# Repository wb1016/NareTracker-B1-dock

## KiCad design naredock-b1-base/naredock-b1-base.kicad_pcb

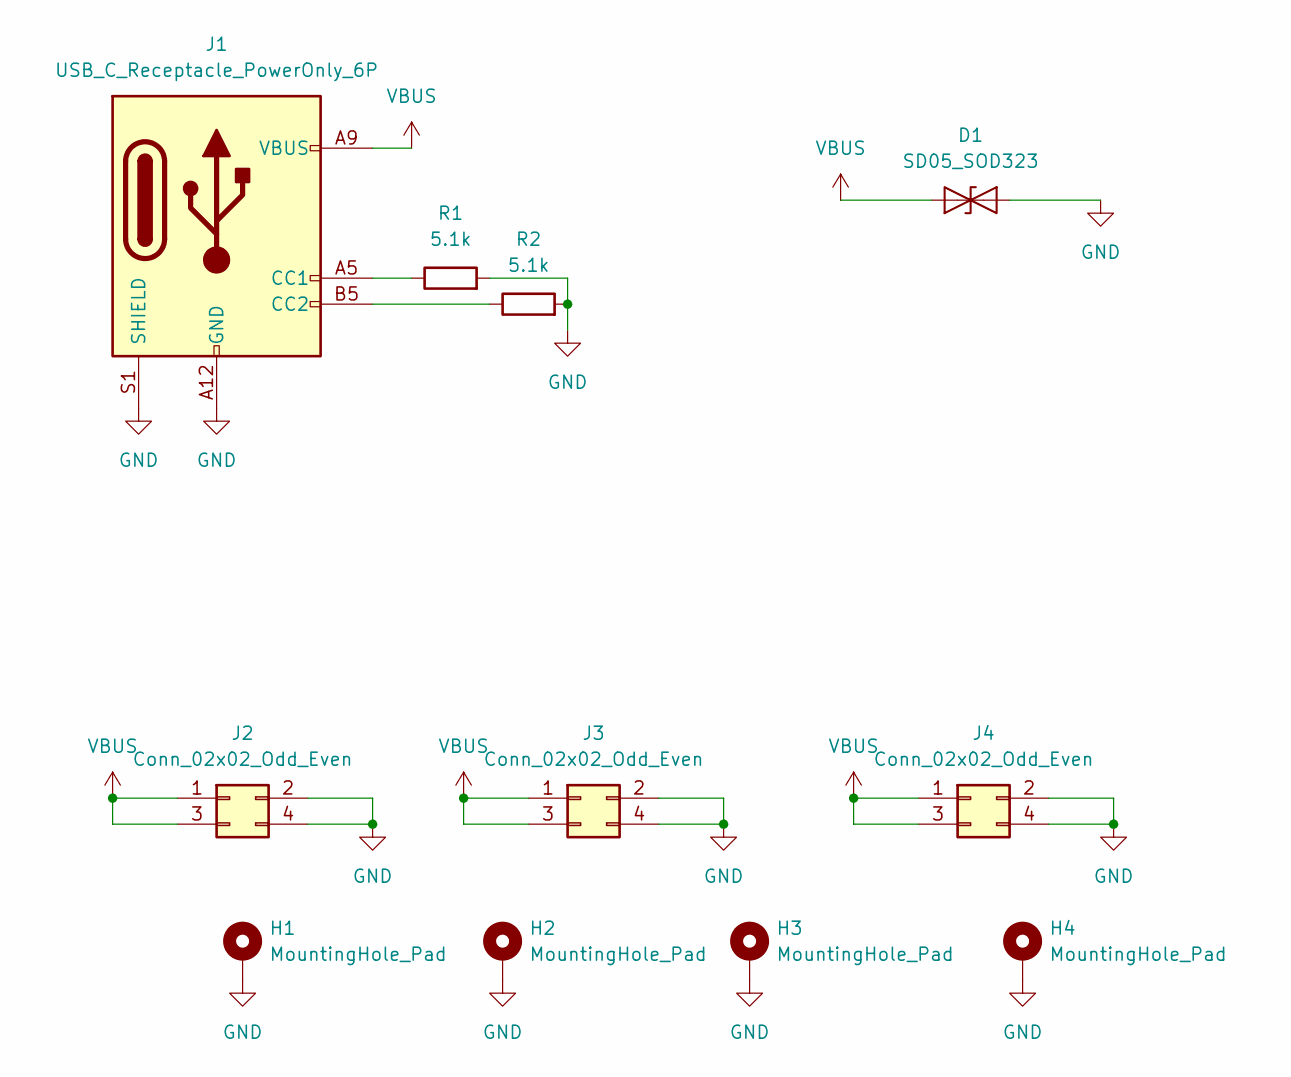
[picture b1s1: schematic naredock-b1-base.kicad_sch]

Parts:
D1: SD05_SOD323; D_SOD-323
H1, H2, H3, H4: MountingHole_Pad; MountingHole_3.2mm_M3_DIN965_Pad
J1: USB_C_Receptacle_PowerOnly_6P; USB_C_Receptacle_GCT_USB4125-xx-x-0190_6P_TopMnt_Horizontal
J2, J3, J4: Conn_02x02_Odd_Even; PinSocket_2x02_P2.54mm_Vertical
R1, R2: 5.1k; R_0402_1005Metric

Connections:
GND: D1.2 (A2), H1.1, H2.1, H3.1, H4.1, J1.A12 (GND), J1.B12 (GND), J1.S1 (SHIELD), J2.2, J2.4, J3.2, J3.4, J4.2, J4.4, R1.2, R2.2
unnamed: J1.A5 (CC1), R1.1
unnamed: J1.B5 (CC2), R2.1
VBUS: D1.1 (A1), J1.A9 (VBUS), J1.B9 (VBUS), J2.1, J2.3, J3.1, J3.3, J4.1, J4.3

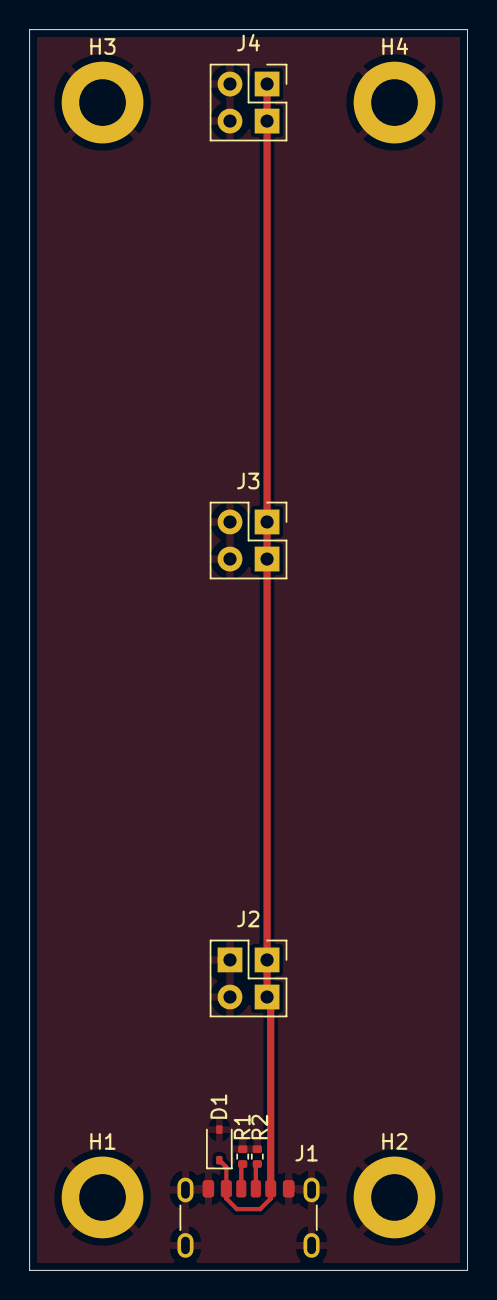
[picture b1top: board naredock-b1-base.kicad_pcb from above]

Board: 2 copper layers, 30.0 x 85.0 mm, 11 parts (0 on the bottom side), 4 nets.

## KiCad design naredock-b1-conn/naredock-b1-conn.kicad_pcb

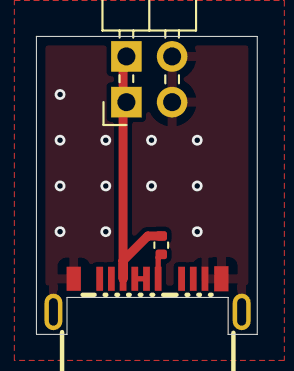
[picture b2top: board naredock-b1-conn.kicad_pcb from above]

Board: 2 copper layers, 12.3 x 16.6 mm, 3 parts (0 on the bottom side), 4 nets.

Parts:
J1: Conn_02x02_Counter_Clockwise; PinHeader_2x02_P2.54mm_Horizontal
R1: 5.1k; R_0402_1005Metric
USB1: GT-USB-8016A; USB-TYPE-C-SMD_GT-USB-8016A

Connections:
GND: J1.3, J1.4, USB1.1 (EH), USB1.2 (EH), USB1.3 (EH), USB1.4 (EH), USB1.A1 (GND)
unnamed: R1.1, USB1.A5 (CC1)
unnamed: USB1.A6 (D+), USB1.A7 (D-)
VBUS: J1.1, J1.2, R1.2, USB1.A9 (VBUS)
